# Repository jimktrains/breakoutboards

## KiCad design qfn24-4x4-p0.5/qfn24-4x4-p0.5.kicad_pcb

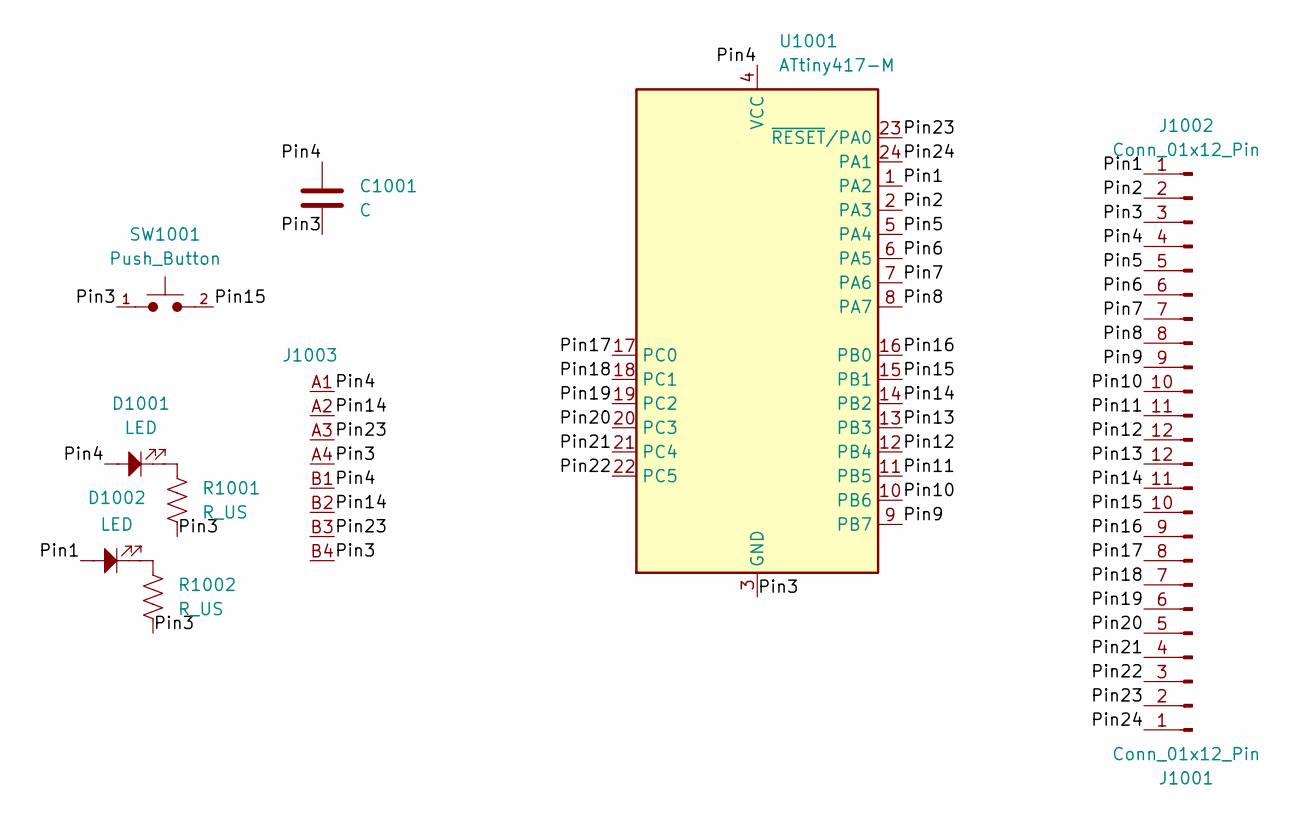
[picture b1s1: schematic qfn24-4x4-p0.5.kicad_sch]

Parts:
C1001: C; C_0402_1005Metric
D1001, D1002: LED; LED_0402_1005Metric
J1001, J1002: Conn_01x12_Pin; PinHeader_1x12_P2.54mm_Vertical
J1003: 8-pin-clip
R1001, R1002: R_US; R_0402_1005Metric
SW1001: Push_Button; SW_PUSH_6mm
U1001: ATtiny417-M; QFN-24-1EP_4x4mm_P0.5mm_EP2.6x2.6mm

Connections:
/Pin1: D1002.2, J1002.1, U1001.1 (PA2)
/Pin2: J1002.2, U1001.2 (PA3)
/Pin3: C1001.2, J1002.3, J1003.A4, J1003.B4, R1001.2, R1002.2, SW1001.1, U1001.3 (GND), U1001.25 (GND)
/Pin4: C1001.1, D1001.2, J1002.4, J1003.A1, J1003.B1, U1001.4 (VCC)
/Pin5: J1002.5, U1001.5 (PA4)
/Pin6: J1002.6, U1001.6 (PA5)
/Pin7: J1002.7, U1001.7 (PA6)
/Pin8: J1002.8, U1001.8 (PA7)
/Pin9: J1002.9, U1001.9 (PB7)
/Pin10: J1002.10, U1001.10 (PB6)
/Pin11: J1002.11, U1001.11 (PB5)
/Pin12: J1002.12, U1001.12 (PB4)
/Pin13: J1001.12, U1001.13 (PB3)
/Pin14: J1001.11, J1003.A2, J1003.B2, U1001.14 (PB2)
/Pin15: J1001.10, SW1001.2, U1001.15 (PB1)
/Pin16: J1001.9, U1001.16 (PB0)
/Pin17: J1001.8, U1001.17 (PC0)
/Pin18: J1001.7, U1001.18 (PC1)
/Pin19: J1001.6, U1001.19 (PC2)
/Pin20: J1001.5, U1001.20 (PC3)
/Pin21: J1001.4, U1001.21 (PC4)
/Pin22: J1001.3, U1001.22 (PC5)
/Pin23: J1001.2, J1003.A3, J1003.B3, U1001.23 (~RESET/PA0)
/Pin24: J1001.1, U1001.24 (PA1)
unnamed: D1001.1, R1001.1
unnamed: D1002.1, R1002.1

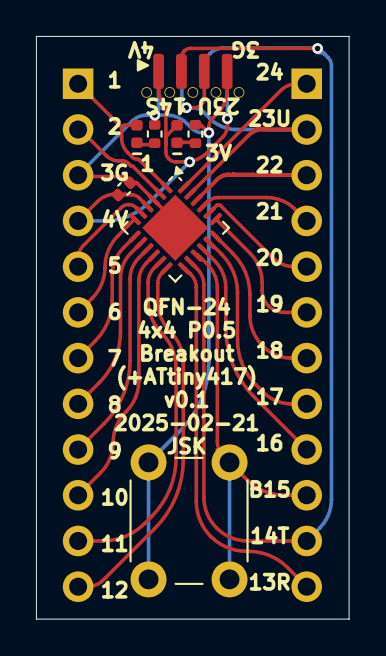
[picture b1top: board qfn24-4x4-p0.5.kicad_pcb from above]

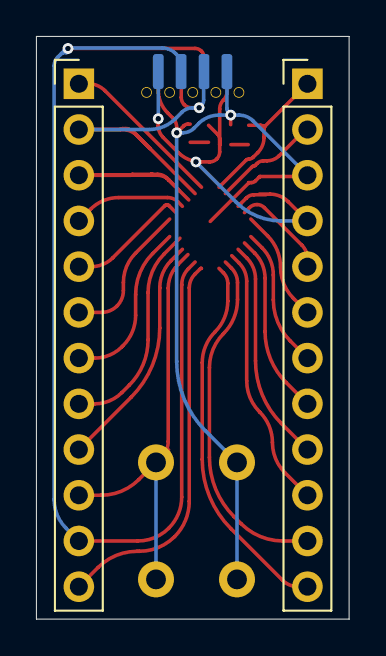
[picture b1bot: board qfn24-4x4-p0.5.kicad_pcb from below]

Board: 2 copper layers, 17.4 x 32.4 mm, 10 parts (2 on the bottom side), 26 nets.
